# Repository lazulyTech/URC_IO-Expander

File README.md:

# UEC Robotics Competition

## [ゲームルール](GameRule/main.pdf)

日本語がレンダリングされないため，ダウンロードしてご利用ください．

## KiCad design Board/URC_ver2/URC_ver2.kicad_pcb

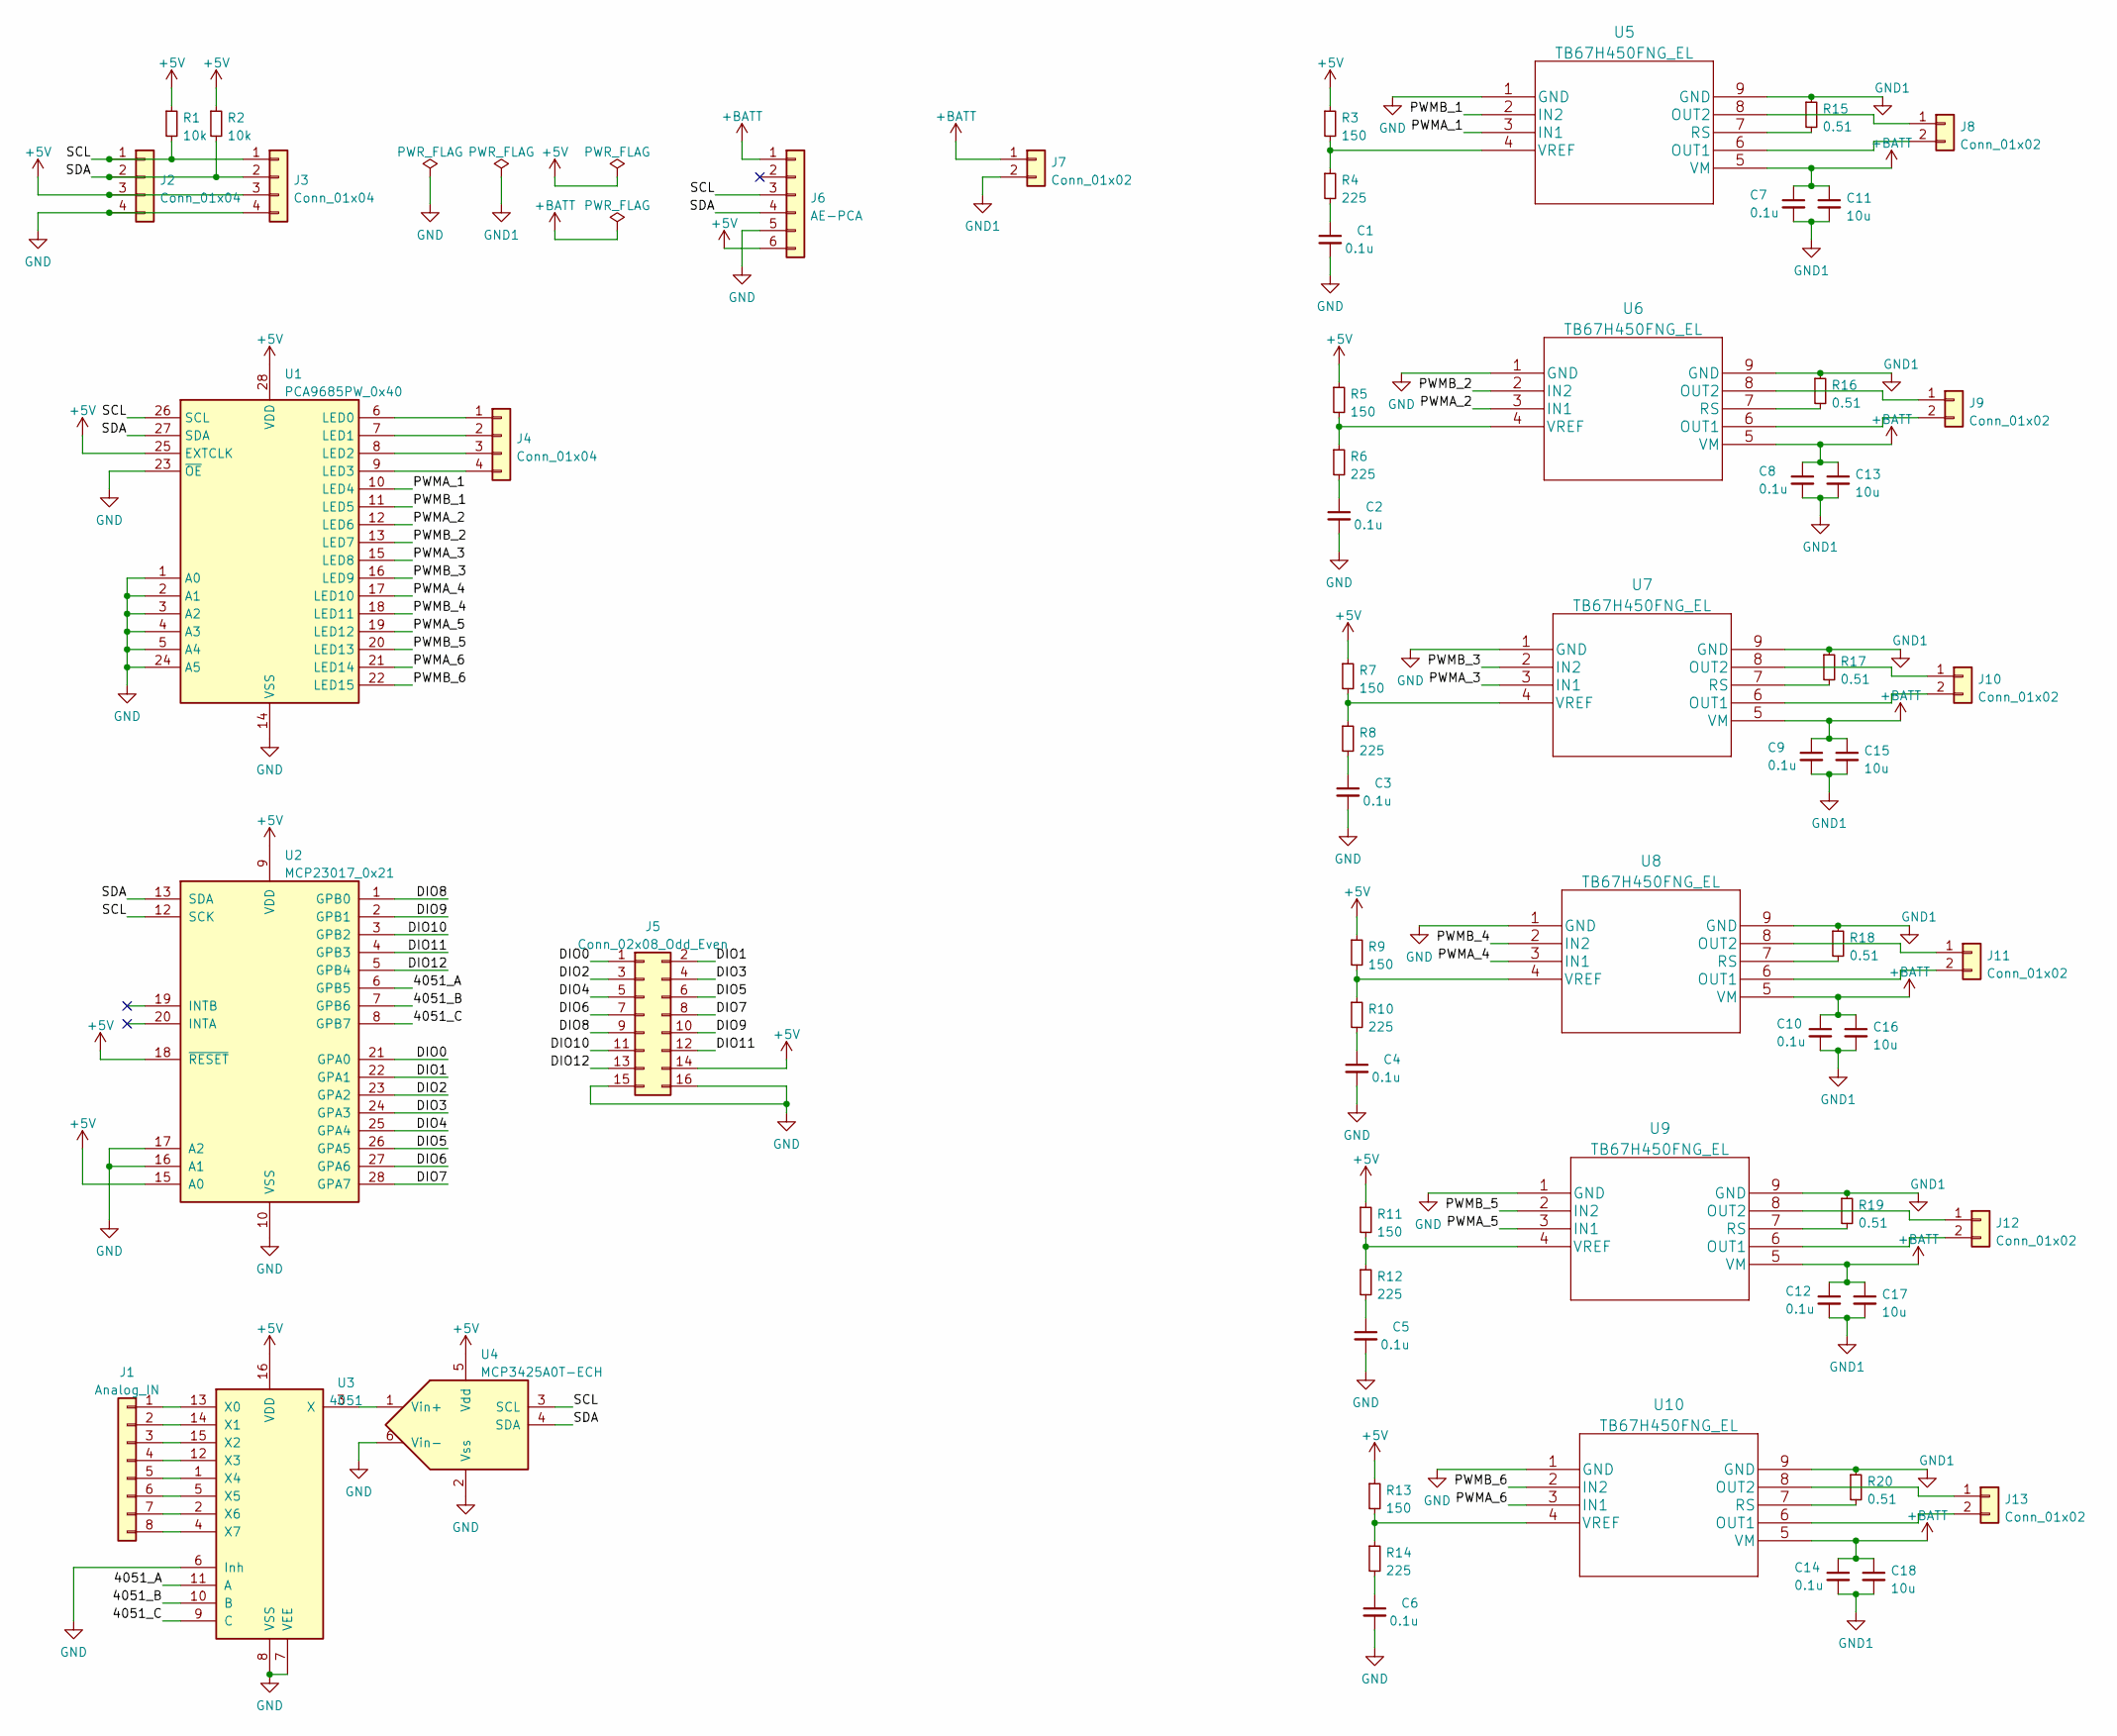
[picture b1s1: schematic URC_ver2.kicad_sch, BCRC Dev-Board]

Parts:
C1, C2, C3, C4, C5, C6, C7, C8, C9, C10, C12, C14: 0.1u; C_0603_1608Metric_Pad1.08x0.95mm_HandSolder
C11, C13, C15, C16, C17, C18: 10u; C_0603_1608Metric_Pad1.08x0.95mm_HandSolder
J1: Analog_IN; PinSocket_1x08_P2.54mm_Vertical
J2: Conn_01x04; NS-Tech_Grove_1x04_P2mm_Vertical
J3, J4: Conn_01x04; PinSocket_1x04_P2.54mm_Vertical
J5: Conn_02x08_Odd_Even; PinSocket_2x08_P2.54mm_Vertical
J6: AE-PCA; PinSocket_1x06_P2.54mm_Vertical
J7, J8, J9, J10, J11, J12, J13: Conn_01x02; JST_XH_B2B-XH-A_1x02_P2.50mm_Vertical
R1, R2: 10k; R_0603_1608Metric_Pad0.98x0.95mm_HandSolder
R3, R5, R7, R9, R11, R13: 150; R_0603_1608Metric_Pad0.98x0.95mm_HandSolder
R4, R6, R8, R10, R12, R14: 225; R_0603_1608Metric_Pad0.98x0.95mm_HandSolder
R15, R16, R17, R18, R19, R20: 0.51; R_Axial_DIN0204_L3.6mm_D1.6mm_P5.08mm_Horizontal
U1: PCA9685PW_0x40; TSSOP-28_4.4x9.7mm_P0.65mm
U2: MCP23017_0x21; DIP-28_W7.62mm
U3: 4051; DIP-16_W7.62mm_LongPads
U4: MCP3425A0T-ECH; SOT-23-6_Handsoldering
U5, U6, U7, U8, U9, U10: TB67H450FNG_EL; TB67H450FNG

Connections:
+5V: J2.3, J3.3, J5.14, J6.6, R1.1, R2.1, R3.1, R5.1, R7.1, R9.1, R11.1, R13.1, U1.25 (EXTCLK), U1.28 (VDD), U2.9 (VDD), U2.15 (A0), U2.18 (~RESET), U3.16 (VDD), U4.5 (Vdd)
+BATT: C7.1, C8.1, C9.1, C10.1, C11.1, C12.1, C13.1, C14.1, C15.1, C16.1, C17.1, C18.1, J6.1, J7.1, U5.5 (VM), U6.5 (VM), U7.5 (VM), U8.5 (VM), U9.5 (VM), U10.5 (VM)
/4051_A: U2.6 (GPB5), U3.11 (A)
/4051_B: U2.7 (GPB6), U3.10 (B)
/4051_C: U2.8 (GPB7), U3.9 (C)
/DIO0: J5.1, U2.21 (GPA0)
/DIO1: J5.2, U2.22 (GPA1)
/DIO2: J5.3, U2.23 (GPA2)
/DIO3: J5.4, U2.24 (GPA3)
/DIO4: J5.5, U2.25 (GPA4)
/DIO5: J5.6, U2.26 (GPA5)
/DIO6: J5.7, U2.27 (GPA6)
/DIO7: J5.8, U2.28 (GPA7)
/DIO8: J5.9, U2.1 (GPB0)
/DIO9: J5.10, U2.2 (GPB1)
/DIO10: J5.11, U2.3 (GPB2)
/DIO11: J5.12, U2.4 (GPB3)
/DIO12: J5.13, U2.5 (GPB4)
/PWMA_1: U1.10 (LED4), U5.3 (IN1)
/PWMA_2: U1.12 (LED6), U6.3 (IN1)
/PWMA_3: U1.15 (LED8), U7.3 (IN1)
/PWMA_4: U1.17 (LED10), U8.3 (IN1)
/PWMA_5: U1.19 (LED12), U9.3 (IN1)
/PWMA_6: U1.21 (LED14), U10.3 (IN1)
/PWMB_1: U1.11 (LED5), U5.2 (IN2)
/PWMB_2: U1.13 (LED7), U6.2 (IN2)
/PWMB_3: U1.16 (LED9), U7.2 (IN2)
/PWMB_4: U1.18 (LED11), U8.2 (IN2)
/PWMB_5: U1.20 (LED13), U9.2 (IN2)
/PWMB_6: U1.22 (LED15), U10.2 (IN2)
/SCL: J2.1, J3.1, J6.3, R1.2, U1.26 (SCL), U2.12 (SCK), U4.3 (SCL)
/SDA: J2.2, J3.2, J6.4, R2.2, U1.27 (SDA), U2.13 (SDA), U4.4 (SDA)
GND: C1.2, C2.2, C3.2, C4.2, C5.2, C6.2, J2.4, J3.4, J5.15, J5.16, J6.5, U1.1 (A0), U1.2 (A1), U1.3 (A2), U1.4 (A3), U1.5 (A4), U1.14 (VSS), U1.23 (~OE), U1.24 (A5), U2.10 (VSS), U2.16 (A1), U2.17 (A2), U3.6 (Inh), U3.7 (VEE), U3.8 (VSS), U4.2 (Vss), U4.6 (Vin-), U5.1 (GND), U6.1 (GND), U7.1 (GND), U8.1 (GND), U9.1 (GND), U10.1 (GND)
GND1: C7.2, C8.2, C9.2, C10.2, C11.2, C12.2, C13.2, C14.2, C15.2, C16.2, C17.2, C18.2, J7.2, R15.1, R16.1, R17.1, R18.1, R19.1, R20.1, U5.9 (GND), U6.9 (GND), U7.9 (GND), U8.9 (GND), U9.9 (GND), U10.9 (GND)
unnamed: C1.1, R4.2
unnamed: C2.1, R6.2
unnamed: C3.1, R8.2
unnamed: C4.1, R10.2
unnamed: C5.1, R12.2
unnamed: C6.1, R14.2
unnamed: J1.1, U3.13 (X0)
unnamed: J1.2, U3.14 (X1)
unnamed: J1.3, U3.15 (X2)
unnamed: J1.4, U3.12 (X3)
unnamed: J1.5, U3.1 (X4)
unnamed: J1.6, U3.5 (X5)
unnamed: J1.7, U3.2 (X6)
unnamed: J1.8, U3.4 (X7)
unnamed: J8.1, U5.8 (OUT2)
unnamed: J8.2, U5.6 (OUT1)
unnamed: J9.1, U6.8 (OUT2)
unnamed: J9.2, U6.6 (OUT1)
unnamed: J10.1, U7.8 (OUT2)
unnamed: J10.2, U7.6 (OUT1)
unnamed: J11.1, U8.8 (OUT2)
unnamed: J11.2, U8.6 (OUT1)
unnamed: J12.1, U9.8 (OUT2)
unnamed: J12.2, U9.6 (OUT1)
unnamed: J13.1, U10.8 (OUT2)
unnamed: J13.2, U10.6 (OUT1)
unnamed: R3.2, R4.1, U5.4 (VREF)
unnamed: R5.2, R6.1, U6.4 (VREF)
unnamed: R7.2, R8.1, U7.4 (VREF)
unnamed: R9.2, R10.1, U8.4 (VREF)
unnamed: R11.2, R12.1, U9.4 (VREF)
unnamed: R13.2, R14.1, U10.4 (VREF)
unnamed: R15.2, U5.7 (RS)
unnamed: R16.2, U6.7 (RS)
unnamed: R17.2, U7.7 (RS)
unnamed: R18.2, U8.7 (RS)
unnamed: R19.2, U9.7 (RS)
unnamed: R20.2, U10.7 (RS)
unnamed: J4.1, U1.6 (LED0)
unnamed: J4.2, U1.7 (LED1)
unnamed: J4.3, U1.8 (LED2)
unnamed: J4.4, U1.9 (LED3)
unnamed: U3.3 (X), U4.1 (Vin+)

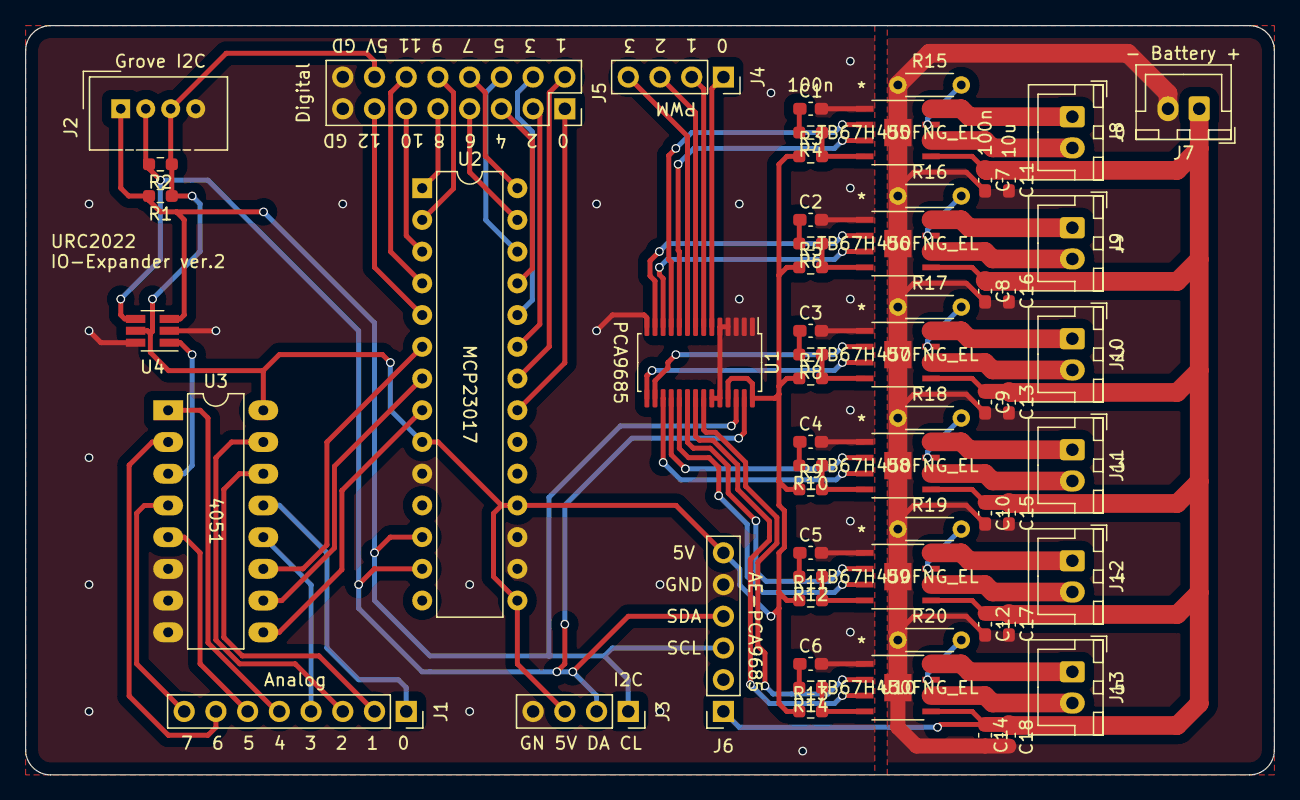
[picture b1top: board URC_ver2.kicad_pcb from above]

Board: 2 copper layers, 100.0 x 60.0 mm, 61 parts (0 on the bottom side), 77 nets.

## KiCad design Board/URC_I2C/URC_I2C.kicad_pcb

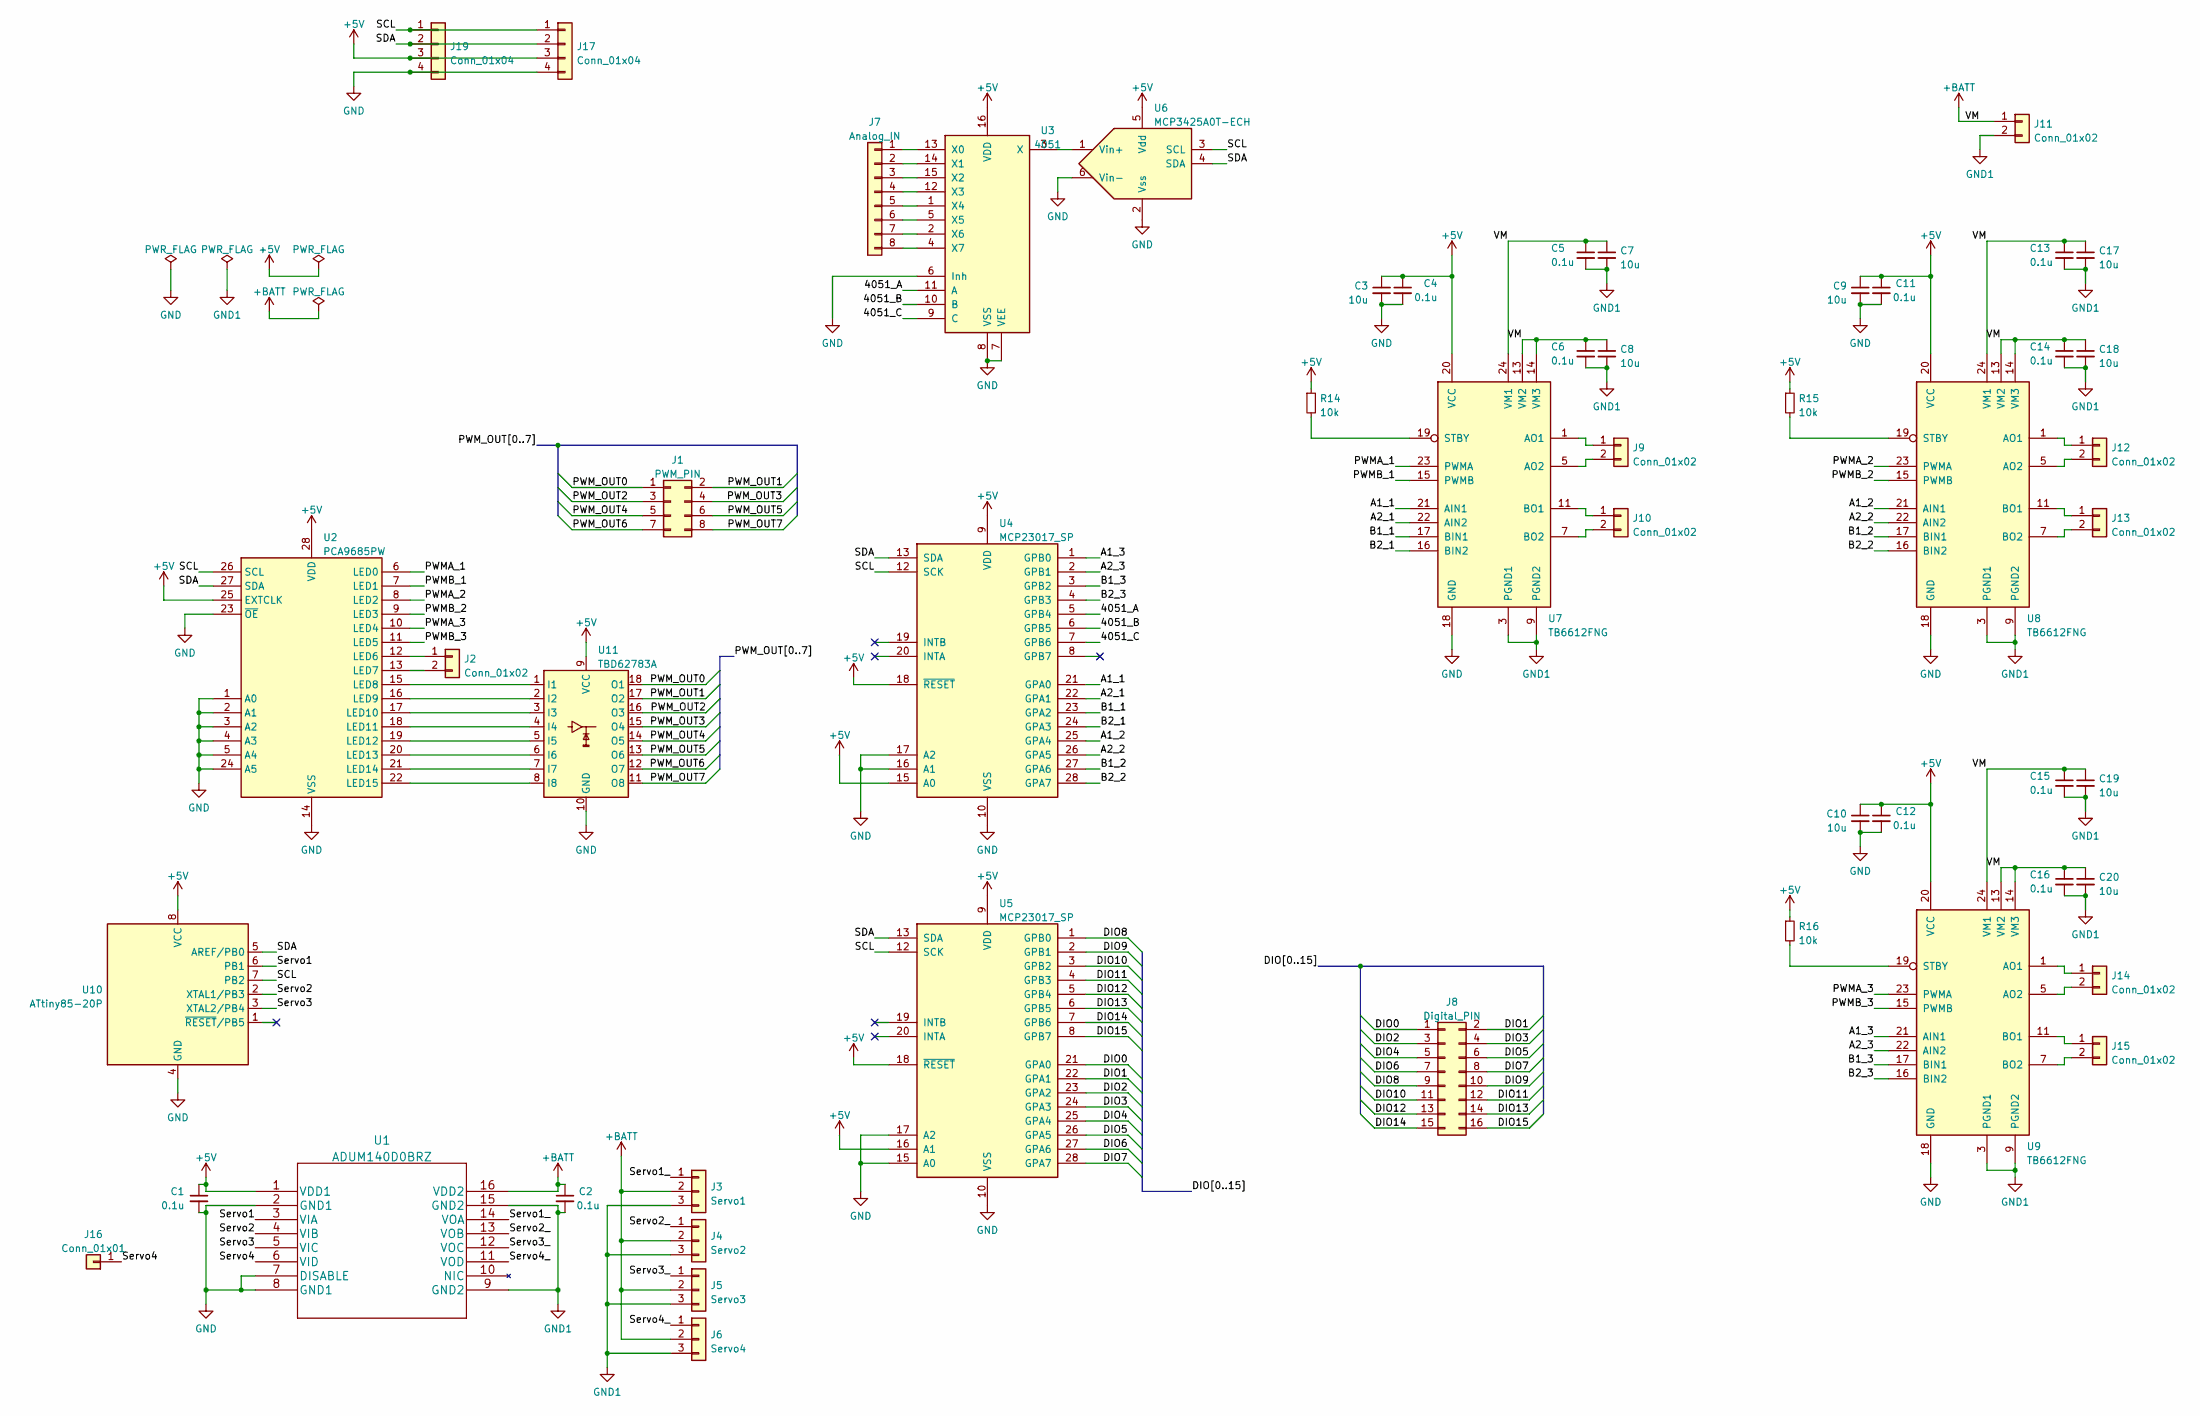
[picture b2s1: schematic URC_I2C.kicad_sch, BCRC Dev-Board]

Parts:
C1, C2, C4, C5, C6, C11, C12, C13, C14, C15, C16: 0.1u; C_0603_1608Metric_Pad1.08x0.95mm_HandSolder
C3, C7, C8, C9, C10, C17, C18, C19, C20: 10u; C_0603_1608Metric_Pad1.08x0.95mm_HandSolder
J1: PWM_PIN; PinSocket_2x04_P2.54mm_Vertical
J2: Conn_01x02; PinSocket_1x02_P2.54mm_Vertical
J3: Servo1; PinHeader_1x03_P2.54mm_Vertical
J4: Servo2; PinHeader_1x03_P2.54mm_Vertical
J5: Servo3; PinHeader_1x03_P2.54mm_Vertical
J6: Servo4; PinHeader_1x03_P2.54mm_Vertical
J7: Analog_IN; PinSocket_1x08_P2.54mm_Vertical
J8: Digital_PIN; PinSocket_2x08_P2.54mm_Vertical
J9, J10, J11, J12, J13, J14, J15: Conn_01x02; JST_XH_B2B-XH-A_1x02_P2.50mm_Vertical
J16: Conn_01x01; PinSocket_1x01_P2.54mm_Vertical
J17: Conn_01x04; PinSocket_1x04_P2.54mm_Vertical
J19: Conn_01x04; NS-Tech_Grove_1x04_P2mm_Vertical
R14, R15, R16: 10k; R_0805_2012Metric_Pad1.20x1.40mm_HandSolder
U1: ADUM140D0BRZ
U2: PCA9685PW; TSSOP-28_4.4x9.7mm_P0.65mm
U3: 4051; DIP-16_W7.62mm_LongPads
U4, U5: MCP23017_SP; DIP-28_W7.62mm
U6: MCP3425A0T-ECH; SOT-23-6_Handsoldering
U7, U8, U9: TB6612FNG; SSOP-24_5.3x8.2mm_P0.65mm
U10: ATtiny85-20P; DIP-8_W7.62mm
U11: TBD62783A; SOP-18_7x12.5mm_P1.27mm

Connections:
+5V: C1.1, C3.1, C4.1, C9.1, C10.1, C11.1, C12.1, J17.3, J19.3, R14.1, R15.1, R16.1, U1.1 (VDD1), U2.25 (EXTCLK), U2.28 (VDD), U3.16 (VDD), U4.9 (VDD), U4.15 (A0), U4.18 (~RESET), U5.9 (VDD), U5.16 (A1), U5.18 (~RESET), U6.5 (Vdd), U7.20 (VCC), U8.20 (VCC), U9.20 (VCC), U10.8 (VCC), U11.9 (VCC)
+BATT: C2.1, C5.1, C6.1, C7.1, C8.1, C13.1, C14.1, C15.1, C16.1, C17.1, C18.1, C19.1, C20.1, J3.2, J4.2, J5.2, J6.2, J11.1, U1.16 (VDD2), U7.13 (VM2), U7.14 (VM3), U7.24 (VM1), U8.13 (VM2), U8.14 (VM3), U8.24 (VM1), U9.13 (VM2), U9.14 (VM3), U9.24 (VM1)
/4051_A: U3.11 (A), U4.5 (GPB4)
/4051_B: U3.10 (B), U4.6 (GPB5)
/4051_C: U3.9 (C), U4.7 (GPB6)
/A1_1: U4.21 (GPA0), U7.21 (AIN1)
/A1_2: U4.25 (GPA4), U8.21 (AIN1)
/A1_3: U4.1 (GPB0), U9.21 (AIN1)
/A2_1: U4.22 (GPA1), U7.22 (AIN2)
/A2_2: U4.26 (GPA5), U8.22 (AIN2)
/A2_3: U4.2 (GPB1), U9.22 (AIN2)
/B1_1: U4.23 (GPA2), U7.17 (BIN1)
/B1_2: U4.27 (GPA6), U8.17 (BIN1)
/B1_3: U4.3 (GPB2), U9.17 (BIN1)
/B2_1: U4.24 (GPA3), U7.16 (BIN2)
/B2_2: U4.28 (GPA7), U8.16 (BIN2)
/B2_3: U4.4 (GPB3), U9.16 (BIN2)
/DIO0: J8.1, U5.21 (GPA0)
/DIO1: J8.2, U5.22 (GPA1)
/DIO2: J8.3, U5.23 (GPA2)
/DIO3: J8.4, U5.24 (GPA3)
/DIO4: J8.5, U5.25 (GPA4)
/DIO5: J8.6, U5.26 (GPA5)
/DIO6: J8.7, U5.27 (GPA6)
/DIO7: J8.8, U5.28 (GPA7)
/DIO8: J8.9, U5.1 (GPB0)
/DIO9: J8.10, U5.2 (GPB1)
/DIO10: J8.11, U5.3 (GPB2)
/DIO11: J8.12, U5.4 (GPB3)
/DIO12: J8.13, U5.5 (GPB4)
/DIO13: J8.14, U5.6 (GPB5)
/DIO14: J8.15, U5.7 (GPB6)
/DIO15: J8.16, U5.8 (GPB7)
/PWMA_1: U2.6 (LED0), U7.23 (PWMA)
/PWMA_2: U2.8 (LED2), U8.23 (PWMA)
/PWMA_3: U2.10 (LED4), U9.23 (PWMA)
/PWMB_1: U2.7 (LED1), U7.15 (PWMB)
/PWMB_2: U2.9 (LED3), U8.15 (PWMB)
/PWMB_3: U2.11 (LED5), U9.15 (PWMB)
/PWM_OUT0: J1.1, U11.18 (O1)
/PWM_OUT1: J1.2, U11.17 (O2)
/PWM_OUT2: J1.3, U11.16 (O3)
/PWM_OUT3: J1.4, U11.15 (O4)
/PWM_OUT4: J1.5, U11.14 (O5)
/PWM_OUT5: J1.6, U11.13 (O6)
/PWM_OUT6: J1.7, U11.12 (O7)
/PWM_OUT7: J1.8, U11.11 (O8)
/SCL: J17.1, J19.1, U2.26 (SCL), U4.12 (SCK), U5.12 (SCK), U6.3 (SCL), U10.7 (PB2)
/SDA: J17.2, J19.2, U2.27 (SDA), U4.13 (SDA), U5.13 (SDA), U6.4 (SDA), U10.5 (AREF/PB0)
/Servo1: U1.3 (VIA), U10.6 (PB1)
/Servo1_: J3.1, U1.14 (VOA)
/Servo2: U1.4 (VIB), U10.2 (XTAL1/PB3)
/Servo2_: J4.1, U1.13 (VOB)
/Servo3: U1.5 (VIC), U10.3 (XTAL2/PB4)
/Servo3_: J5.1, U1.12 (VOC)
/Servo4: J16.1, U1.6 (VID)
/Servo4_: J6.1, U1.11 (VOD)
GND: C1.2, C3.2, C4.2, C9.2, C10.2, C11.2, C12.2, J17.4, J19.4, U1.2 (GND1), U1.7 (DISABLE), U1.8 (GND1), U2.1 (A0), U2.2 (A1), U2.3 (A2), U2.4 (A3), U2.5 (A4), U2.14 (VSS), U2.23 (~OE), U2.24 (A5), U3.6 (Inh), U3.7 (VEE), U3.8 (VSS), U4.10 (VSS), U4.16 (A1), U4.17 (A2), U5.10 (VSS), U5.15 (A0), U5.17 (A2), U6.2 (Vss), U6.6 (Vin-), U7.18 (GND), U8.18 (GND), U9.18 (GND), U10.4 (GND), U11.10 (GND)
GND1: C2.2, C5.2, C6.2, C7.2, C8.2, C13.2, C14.2, C15.2, C16.2, C17.2, C18.2, C19.2, C20.2, J3.3, J4.3, J5.3, J6.3, J11.2, U1.9 (GND2), U1.15 (GND2), U7.3 (PGND1), U7.4 (PGND1), U7.9 (PGND2), U7.10 (PGND2), U8.3 (PGND1), U8.4 (PGND1), U8.9 (PGND2), U8.10 (PGND2), U9.3 (PGND1), U9.4 (PGND1), U9.9 (PGND2), U9.10 (PGND2)
unnamed: J2.1, U2.12 (LED6)
unnamed: J2.2, U2.13 (LED7)
unnamed: J7.1, U3.13 (X0)
unnamed: J7.2, U3.14 (X1)
unnamed: J7.3, U3.15 (X2)
unnamed: J7.4, U3.12 (X3)
unnamed: J7.5, U3.1 (X4)
unnamed: J7.6, U3.5 (X5)
unnamed: J7.7, U3.2 (X6)
unnamed: J7.8, U3.4 (X7)
unnamed: J9.1, U7.1 (AO1), U7.2 (AO1)
unnamed: J9.2, U7.5 (AO2), U7.6 (AO2)
unnamed: J10.1, U7.11 (BO1), U7.12 (BO1)
unnamed: J10.2, U7.7 (BO2), U7.8 (BO2)
unnamed: J12.1, U8.1 (AO1), U8.2 (AO1)
unnamed: J12.2, U8.5 (AO2), U8.6 (AO2)
unnamed: J13.1, U8.11 (BO1), U8.12 (BO1)
unnamed: J13.2, U8.7 (BO2), U8.8 (BO2)
unnamed: J14.1, U9.1 (AO1), U9.2 (AO1)
unnamed: J14.2, U9.5 (AO2), U9.6 (AO2)
unnamed: J15.1, U9.11 (BO1), U9.12 (BO1)
unnamed: J15.2, U9.7 (BO2), U9.8 (BO2)
unnamed: R14.2, U7.19 (STBY)
unnamed: R15.2, U8.19 (STBY)
unnamed: R16.2, U9.19 (STBY)
unnamed: U3.3 (X), U6.1 (Vin+)
unnamed: U2.15 (LED8), U11.1 (I1)
unnamed: U2.16 (LED9), U11.2 (I2)
unnamed: U2.17 (LED10), U11.3 (I3)
unnamed: U2.18 (LED11), U11.4 (I4)
unnamed: U2.19 (LED12), U11.5 (I5)
unnamed: U2.20 (LED13), U11.6 (I6)
unnamed: U2.21 (LED14), U11.7 (I7)
unnamed: U2.22 (LED15), U11.8 (I8)

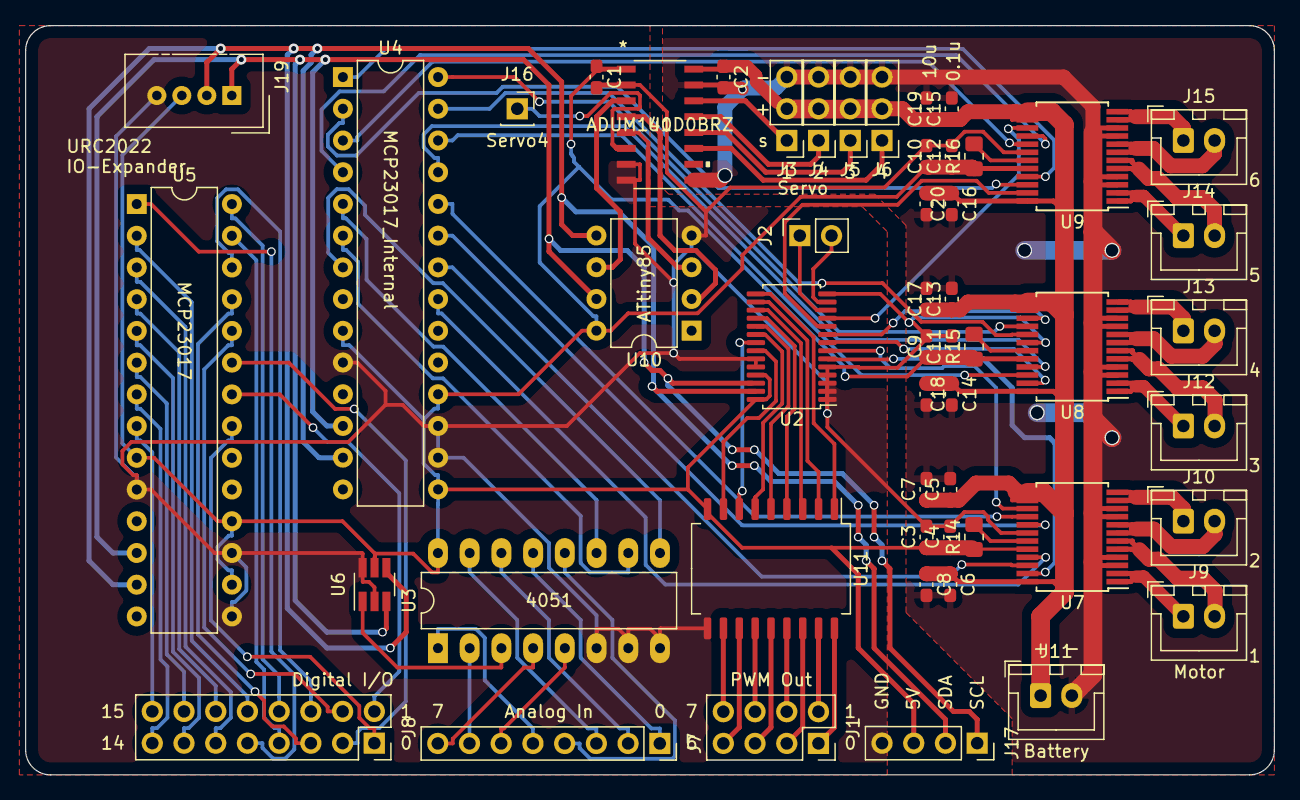
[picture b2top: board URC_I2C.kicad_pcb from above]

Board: 2 copper layers, 100.0 x 60.0 mm, 52 parts (0 on the bottom side), 93 nets.

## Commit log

2022-06-05 拡張基板を作成
2022-06-17 ゲームルールをアップロード
2022-06-17 ゲームルールを更新
2022-06-27 Firmwareのgitignoreを追加
2022-06-27 Firmware Base
2022-06-27 RobotSystemを移動
2022-06-29 Host
2022-06-29 M5StickC Firmwareの更新
2022-06-29 imgを追加
2022-06-29 README.mdを更新
2022-07-04 update M5StickC Firmware
2022-07-04 update Host Firmware
2022-07-04 submodule
2022-07-04 Edit .gitignore
2022-07-04 Revert "Edit .gitignore"
    This reverts commit 59cdcaa725f07a5d78210959ebc8a1b654b1b952.
2022-07-04 Revert "submodule"
    This reverts commit d2ffcac75983989f2968498498ca5c2a661b54b8.
2022-07-22 ファームウェアアップデート
2022-07-22 基板アップデート

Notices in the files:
parts and their libraries:
Copyright 2021 Accelerated Designs. All rights reserved.
